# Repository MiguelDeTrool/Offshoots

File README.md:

# Offshoots

Offshoots is an easy to DIY, Arduino Nano based adaptation of
Mutable Instruments' Branches. Heavily inspired by [sound-force.nl's Through-Hole Braids](https://sound-force.nl/?page_id=3179) and [Quinie.nl's NanoGris](https://github.com/Quinienl/NanoGris).

Only functional difference with Branches is Offshoots doesn't "remember" which output is high when leaving latch mode and coming back to it again. It needs a new input to latch to one of the outputs.

The photos included are of the prototype version of the board. I messed up the silkscreen, but that has been corrected. If you have some boards made, please send me photos! I also corrected a couple of other minor errors, so technically, this version of the board on github is untested, but I am very confident it works as intended.

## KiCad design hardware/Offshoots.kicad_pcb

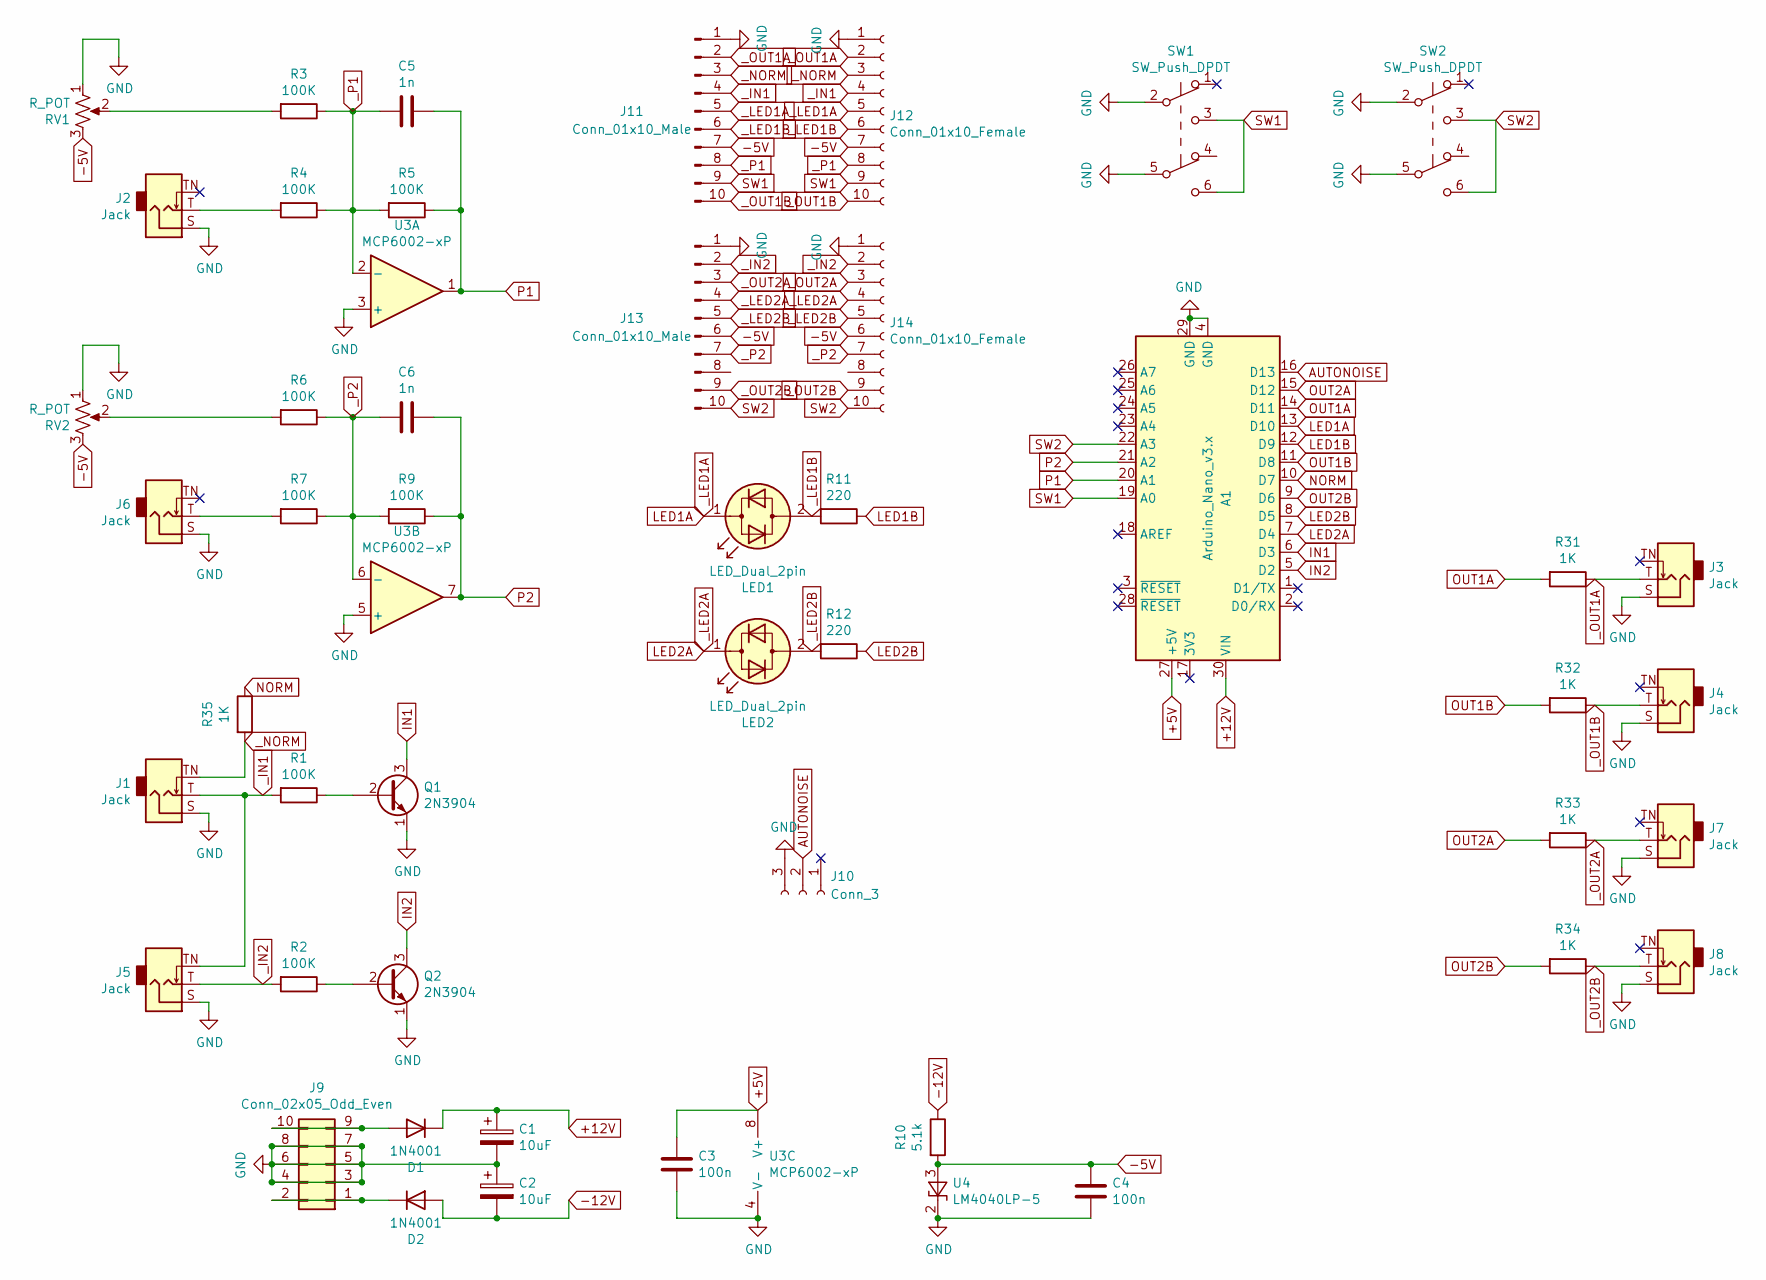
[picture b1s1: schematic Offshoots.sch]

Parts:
A1: Arduino_Nano_v3.x; Arduino_Nano
C1, C2: 10uF; CP_Radial_D6.3mm_P2.50mm
C3, C4: 100n; C_Disc_D5.0mm_W2.5mm_P2.50mm
C5, C6: 1n; C_Disc_D5.0mm_W2.5mm_P2.50mm
D1, D2: 1N4001; D_DO-41_SOD81_P7.62mm_Horizontal
J1, J2, J3, J4, J5, J6, J7, J8: Jack; ModdedThonkiconn
J9: Conn_02x05_Odd_Even; IDC-Header_2x05_P2.54mm_Vertical
J10: Conn_3; PinHeader_1x03_P2.54mm_Vertical
J11, J13: Conn_01x10_Male; PinHeader_1x10_P2.54mm_Vertical
J12, J14: Conn_01x10_Female; PinHeader_1x10_P2.54mm_Vertical
LED1, LED2: LED_Dual_2pin; LED_D3.0mm
Q1, Q2: 2N3904; TO-92L_Inline_Wide
R1, R2, R3, R4, R5, R6, R7, R9: 100K; R_Axial_DIN0207_L6.3mm_D2.5mm_P7.62mm_Horizontal
R10: 5.1k; R_Axial_DIN0207_L6.3mm_D2.5mm_P7.62mm_Horizontal
R11, R12: 220; R_Axial_DIN0207_L6.3mm_D2.5mm_P7.62mm_Horizontal
R31, R32, R33, R34, R35: 1K; R_Axial_DIN0207_L6.3mm_D2.5mm_P7.62mm_Horizontal
RV1, RV2: R_POT; ModdedPotentiometer
SW1, SW2: SW_Push_DPDT; DPDT_Momentary_Push_Button_Switch
U3: MCP6002-xP; DIP-8_W7.62mm_LongPads
U4: LM4040LP-5; TO-92L_Inline_Wide

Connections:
+5V: A1.27 (+5V), C3.2, U3.8 (V+)
+12V: A1.30 (VIN), C1.1, D1.1 (K)
-5V: C4.2, J11.7, J12.7, J13.6, J14.6, R10.2, RV1.3, RV2.3, U4.3 (A)
-12V: C2.2, D2.2 (A), R10.1
AUTONOISE: A1.16 (D13), J10.2
GND: A1.4 (GND), A1.29 (GND), C1.2, C2.1, C3.1, C4.1, J1.S, J2.S, J3.S, J4.S, J5.S, J6.S, J7.S, J8.S, J9.3, J9.4, J9.5, J9.6, J9.7, J9.8, J10.3, J11.1, J12.1, J13.1, J14.1, Q1.1 (E), Q2.1 (E), RV1.1, RV2.1, SW1.2 (B), SW1.5 (B), SW2.2 (B), SW2.5 (B), U3.3 (+), U3.4 (V-), U3.5 (+), U4.2 (K)
IN1: A1.6 (D3), Q1.3 (C)
IN2: A1.5 (D2), Q2.3 (C)
LED1A: A1.13 (D10), J11.5, J12.5, LED1.1 (KA)
LED1B: A1.12 (D9), R11.1
LED2A: A1.7 (D4), J13.4, J14.4, LED2.1 (KA)
LED2B: A1.8 (D5), R12.1
NORM: A1.10 (D7), R35.1
unnamed: D1.2 (A), J9.9, J9.10
unnamed: D2.1 (K), J9.1, J9.2
unnamed: J2.T, R4.2
unnamed: J6.T, R7.2
unnamed: Q1.2 (B), R1.1
unnamed: Q2.2 (B), R2.1
unnamed: R3.2, RV1.2
unnamed: R6.2, RV2.2
OUT1A: A1.14 (D11), R31.2
OUT1B: A1.11 (D8), R32.2
OUT2A: A1.15 (D12), R33.2
OUT2B: A1.9 (D6), R34.2
P1: A1.20 (A1), C5.1, R5.1, U3.1
P2: A1.21 (A2), C6.1, R9.1, U3.7
SW1: A1.19 (A0), J11.9, J12.9, SW1.3 (C), SW1.6 (C)
SW2: A1.22 (A3), J13.10, J14.10, SW2.3 (C), SW2.6 (C)
_IN1: J1.T, J5.TN, J11.4, J12.4, R1.2
_IN2: J5.T, J13.2, J14.2, R2.2
_LED1B: J11.6, J12.6, LED1.2 (AK), R11.2
_LED2B: J13.5, J14.5, LED2.2 (AK), R12.2
_NORM: J1.TN, J11.3, J12.3, R35.2
_OUT1A: J3.T, J11.2, J12.2, R31.1
_OUT1B: J4.T, J11.10, J12.10, R32.1
_OUT2A: J7.T, J13.3, J14.3, R33.1
_OUT2B: J8.T, J13.9, J14.9, R34.1
_P1: C5.2, J11.8, J12.8, R3.1, R4.1, R5.2, U3.2 (-)
_P2: C6.2, J13.7, J14.7, R6.1, R7.1, R9.2, U3.6 (-)

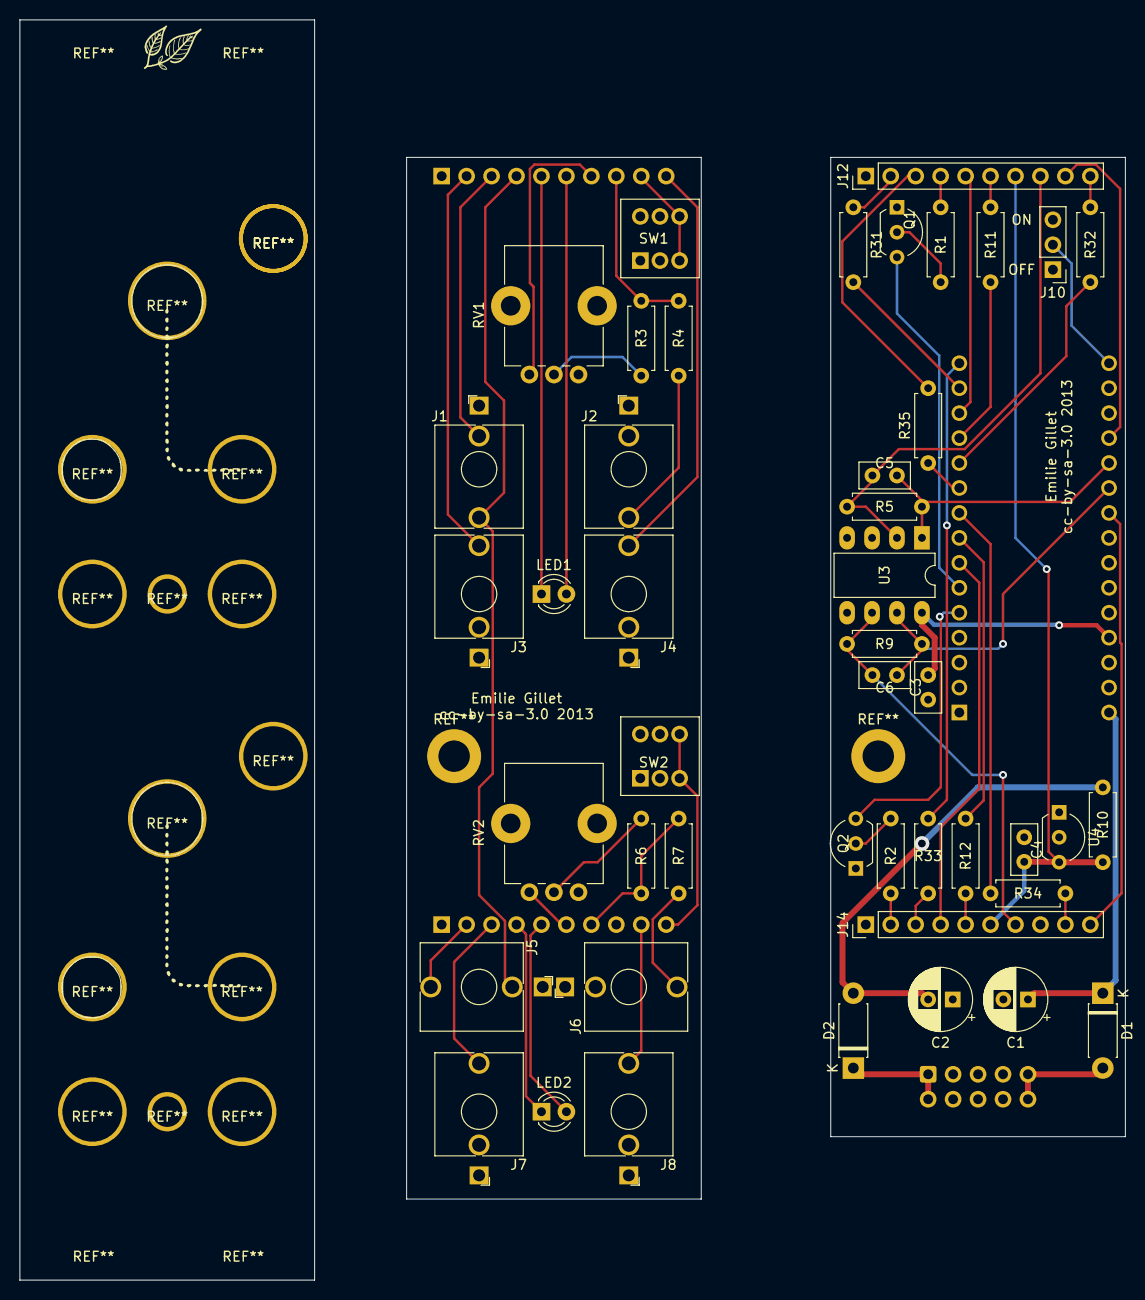
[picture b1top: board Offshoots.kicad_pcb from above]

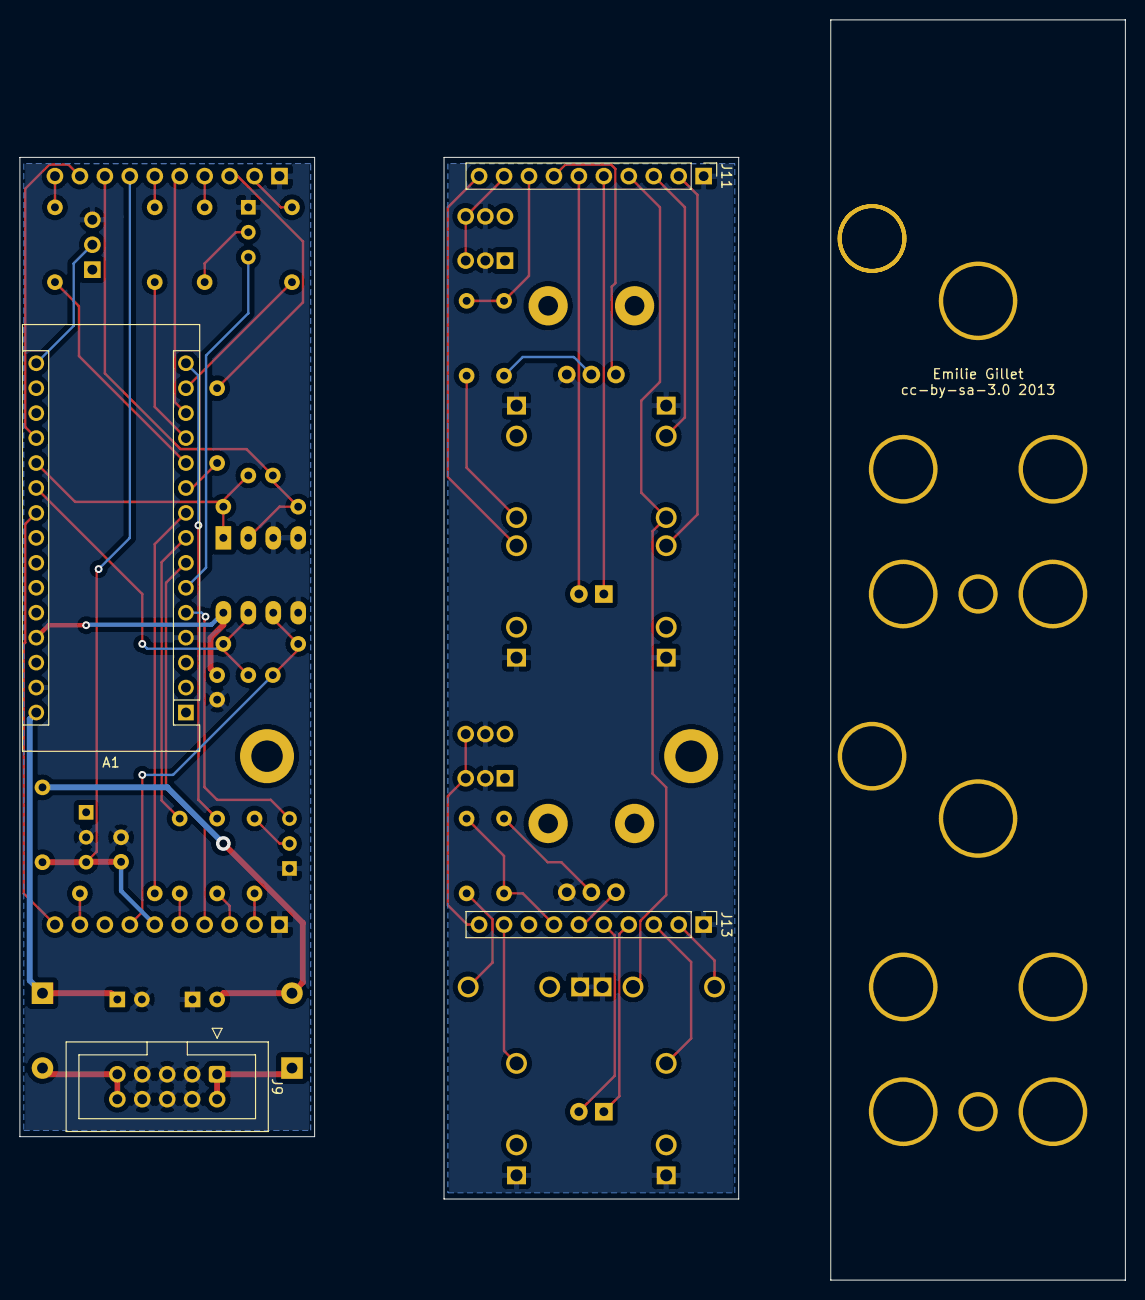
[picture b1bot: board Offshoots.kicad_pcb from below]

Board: 2 copper layers, 112.6 x 128.3 mm, 49 parts (4 on the bottom side), 40 nets.

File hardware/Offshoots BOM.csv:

Designator,Package,Quantity,Designation,"Tayda link, notes"
"J12,J14",PinHeader_1x10_P2.54mm_Vertical,2,Conn_01x10_Female,https://www.taydaelectronics.com/40-pin-2-54-mm-single-row-f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
"J11,J13",PinHeader_1x10_P2.54mm_Vertical,2,Conn_01x10_Male,https://www.taydaelectronics.com/40-pin-2-54-mm-single-row-p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
J10,PinHeader_1x03_P2.54mm_Vertical,1,Conn_01x03_Male,"same as previous, no need to order extra"
J9,IDC-Header_2x05_P2.54mm_Vertical,1,Conn_02x05_Odd_Even,https://www.taydaelectronics.com/10-pin-box-header-connector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
"D1,D2",D_DO-41_SOD81_P7.62mm_Horizontal,2,1N4001,https://www.taydaelectronics.com/1n4001-diode-1a-50v.html
"Q1,Q2",TO-92L_Inline_Wide,2,2N3904,https://www.taydaelectronics.com/2n3904-npn-general-propose-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
"R1,R2,R3,R4,R5,R6,R7,R9",R_Axial_DIN0207_L6.3mm_D2.5mm_P7.62mm_Horizontal,8,100K,https://www.taydaelectronics.com/10-x-resistor-100k-ohm-1-4w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
"R32,R32,R33,R34,R35",R_Axial_DIN0207_L6.3mm_D2.5mm_P10.16mm_Horizontal,5,1K,https://www.taydaelectronics.com/10-x-resistor-1k-ohm-1-4w-1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
"R11,R12",R_Axial_DIN0207_L6.3mm_D2.5mm_P10.16mm_Horizontal,2,220R,https://www.taydaelectronics.com/resistor-220-ohm-1-4w-1-met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
R10,R_Axial_DIN0207_L6.3mm_D2.5mm_P10.16mm_Horizontal,1,"5,1K",https://www.taydaelectronics.com/resistor-5-1k-ohm-1-4w-1-me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
"C5,C6",C_Disc_D5.0mm_W2.5mm_P2.50mm,2,1nF ceramic,https://www.taydaelectronics.com/10-1nf-50v-ceramic-disc-cap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
"C3,C4",C_Disc_D5.0mm_W2.5mm_P2.50mm,2,100nF ceramic,https://www.taydaelectronics.com/a-553-0-1uf-50v-ceramic-dis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
"C1,C2",CP_Radial_D6.3mm_P2.50mm,2,10uF electrolytic,https://www.taydaelectronics.com/10uf-35v-105c-radial-electr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
U4,TO-92L_Inline_Wide,1,"LM4040LP-5 (or 10V Zener, see notes)",https://www.taydaelectronics.com/1n4740a-1n4740-zener-diode-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
U3,DIP-8_W7.62mm_LongPads,1,MCP6002-xP,"NOT AVAILABLE from tayda. I may make another version that uses non rail-to-rail op-amps, like MCP602 or LM358. If you use them in current design you don’t get the full pot range"
"SW1,SW2",DPDT_Momentary_Push_Button_Switch,2,SW_Push_DPDT_Latching,https://www.taydaelectronics.com/push-button-switch-latching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
"RV1,RV2",Potentiometer,2,R_POT 10k,https://www.taydaelectronics.com/tayda-10k-ohm-linear-taper-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
"J1,J2,J3,J4,J5,J6,J7,J8",Thonkiconn,8,Jack,https://www.taydaelectronics.com/pj-3001f-3-5-mm-mono-phone-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
"LED1,LED2",LED_D3.0mm,2,LED_Bicolor_2pin,https://www.taydaelectronics.com/bi-color-led-3mm-red-green.html
A1,Arduino_Nano,1,Arduino_Nano,"https://www.taydaelectronics.com/nano-3-0-controller-compati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 Out of stock currently at tayda, but available from many places"
,,,,
EXTRAS,PinHeader_1x15_P2.54mm_Vertical,2,Headers for Arduino Nano,https://www.taydaelectronics.com/15-pin-2-54-mm-single-row-f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
,Push Button Switch Caps White Color 6x5mm,2,Button Caps,https://www.taydaelectronics.com/push-button-switch-caps-whi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
,Knob DAVIES 1900H CLONE White,2,Knobs for pots,https://www.taydaelectronics.com/knob-davies-1900h-clone-white.html
,Mini Jumper 2.54mm Gold Plated Closed Cover,1,Jumper for auto-gate config,https://www.taydaelectronics.com/mini-jumper-2-54mm-gold-pla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 OR https://www.taydaelectronics.com/mini-jumper-2-00mm-gold-pla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
,8 pin DIP IC Socket Adaptor Solder Type,1,Socket for MCP6002,https://www.taydaelectronics.com/8-pin-dip-ic-socket-adaptor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
,,,,
NOTES,,,,"Total cost of Tayda cart with the Arduino is about $10, without it’s about $6,3. CHEAP!"
,,,,"The amount needed for tayda ordering may differ, ex: you only need to order one 40 pin header strip and cut to right sizes"
,,,,"You may have to experiment with lower values for R10, until you get -5V at the anode (pin 3) of the LM4040"
,,,,"You can replace the expensive and hard to source LM4040LP-5 with a 10V Zener, you just have to replace R3 and R6 with 200k resistors. The Zener and resistors and 14 cents to the cart"
,,,,LED orientation isn’t vital so long as it’s consistent. Use LED orientation indicated on PCB (shorter lead to square pad) to have original Branches colors
,,,,Switch orientation isn’t vital so long as it’s consistent. Just changes which mode corresponds to pushed/unpushed position
,,,,"You could just use 1K resistors for R11 and R12, it would save ordering extra. It just makes LEDs slightly duller"
,,,,"You can get two 6mm M3 screws and a 11mm M3 standoff to hold the control and brain boars together, but I don’t find them necessary"
,,,,"Auto-gate generation isn’t implemented yet, might never be"

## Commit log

2021-09-06 Create null
2021-09-06 Update LICENSE

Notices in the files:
hardware/Offshoots.kicad_pcb:
cc-by-sa-3.0 2013
